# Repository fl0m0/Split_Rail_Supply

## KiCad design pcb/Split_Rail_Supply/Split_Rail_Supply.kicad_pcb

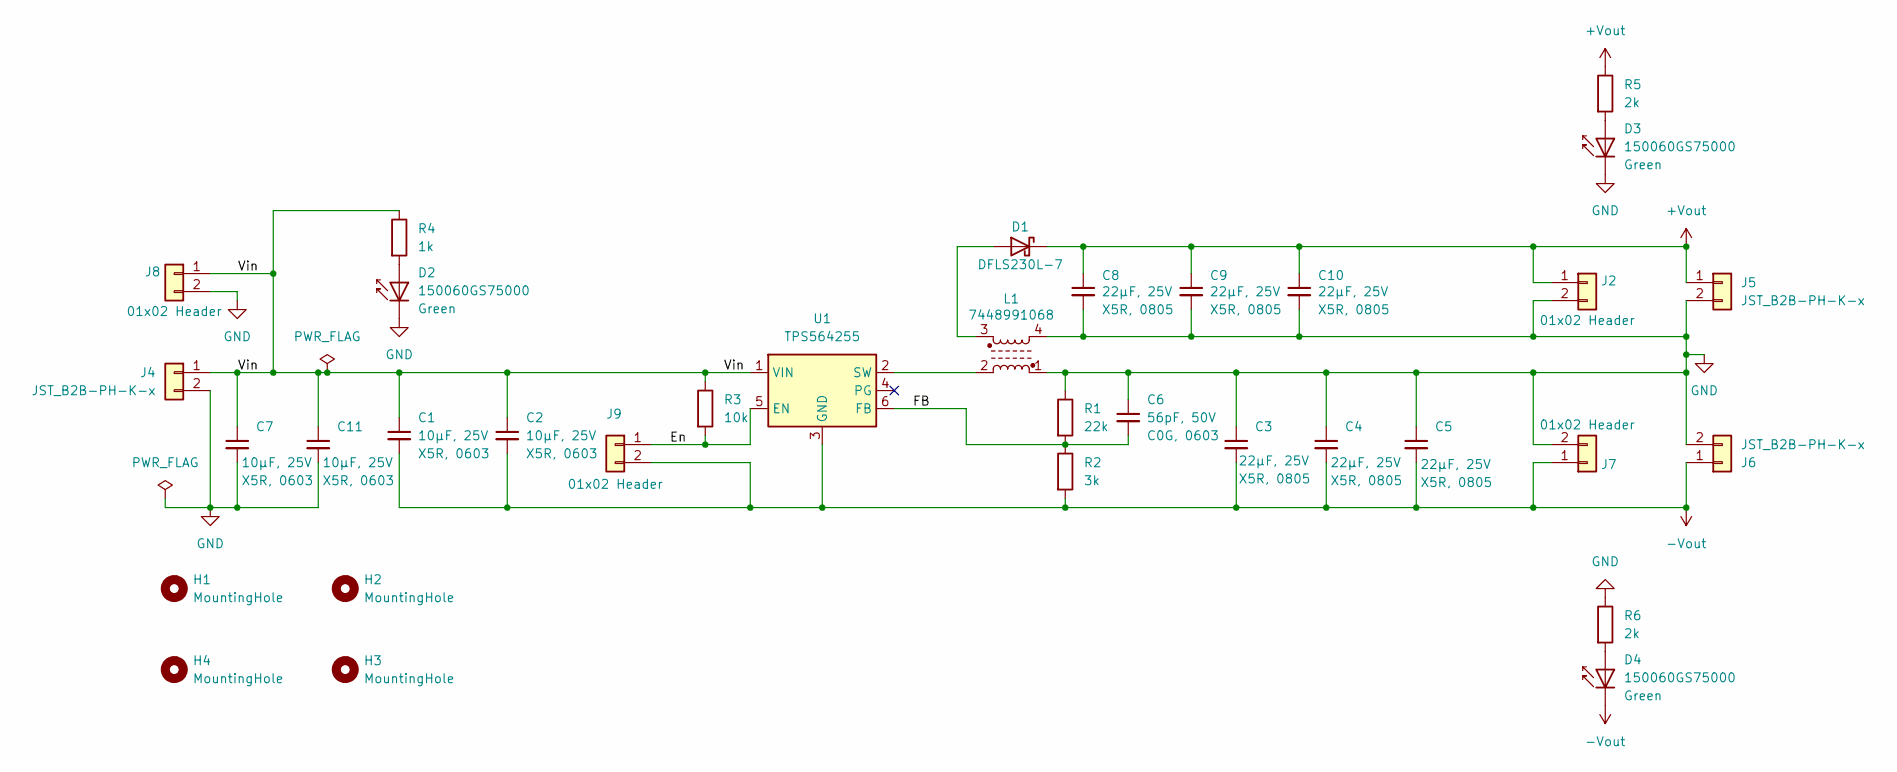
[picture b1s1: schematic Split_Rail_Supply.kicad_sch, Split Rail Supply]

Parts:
C1, C2, C7, C11: 10uF,25V,X5R,0603; C_0603_1608Metric_Pad1.08x0.95mm_HandSolder
C3, C4, C5, C8, C9, C10: 22uF,25V,X5R,0805; C_0805_2012Metric_Pad1.18x1.45mm_HandSolder
C6: 56pF,50V,C0G,0603; C_0603_1608Metric_Pad1.08x0.95mm_HandSolder
D1: DFLS230L-7; D_PowerDI-123; MPN DFLS230L-7
D2, D3, D4: 150060GS75000; LED_0603_1608Metric_Pad1.05x0.95mm_HandSolder
H1, H2, H3, H4: MountingHole; MountingHole_2.7mm_M2.5_DIN965
J2, J7, J8, J9: Header_01x02_Wurth_61300211121; PinHeader_1x02_P2.54mm_Vertical; MPN 61300211121
J4, J5, J6: JST_B2B-PH-K-x; JST_PH_B2B-PH-K_1x02_P2.00mm_Vertical; MPN B2B-PH-K-S(LF)(SN)
L1: 7448991068; L_Wuerth_WE-MCRI-1040_Handsoldering; MPN 7448991068
R1: 22k,0603; R_0603_1608Metric_Pad0.98x0.95mm_HandSolder; Tolerance 1%
R2: 3k,0603; R_0603_1608Metric_Pad0.98x0.95mm_HandSolder; Tolerance 1%
R3: 10k,0603; R_0603_1608Metric_Pad0.98x0.95mm_HandSolder; Tolerance 1%
R4: 1k,0603; R_0603_1608Metric_Pad0.98x0.95mm_HandSolder; Tolerance 1%
R5, R6: 2k,0603; R_0603_1608Metric_Pad0.98x0.95mm_HandSolder; Tolerance 1%
U1: TPS564255; SOT-563; MPN TPS564255DRLR

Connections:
+Vout: C8.1, C9.1, C10.1, D1.1 (K), J2.1, J5.1, R5.1
-Vout: C1.2, C2.2, C3.2, C4.2, C5.2, D4.1 (K), J6.1, J7.1, J9.2, R2.2, U1.3 (GND)
/En: J9.1, R3.2, U1.5 (EN)
/FB: C6.2, R1.2, R2.1, U1.6 (FB)
/Vin: C1.1, C2.1, C7.1, C11.1, J4.1, J8.1, R3.1, R4.1, U1.1 (VIN)
GND: C3.1, C4.1, C5.1, C6.1, C7.2, C8.2, C9.2, C10.2, C11.2, D2.1 (K), D3.1 (K), J2.2, J4.2, J5.2, J6.2, J7.2, J8.2, L1.1, L1.4, R1.1, R6.1
unnamed: D1.2 (A), L1.3
unnamed: D2.2 (A), R4.2
unnamed: D3.2 (A), R5.2
unnamed: D4.2 (A), R6.2
unnamed: L1.2, U1.2 (SW)

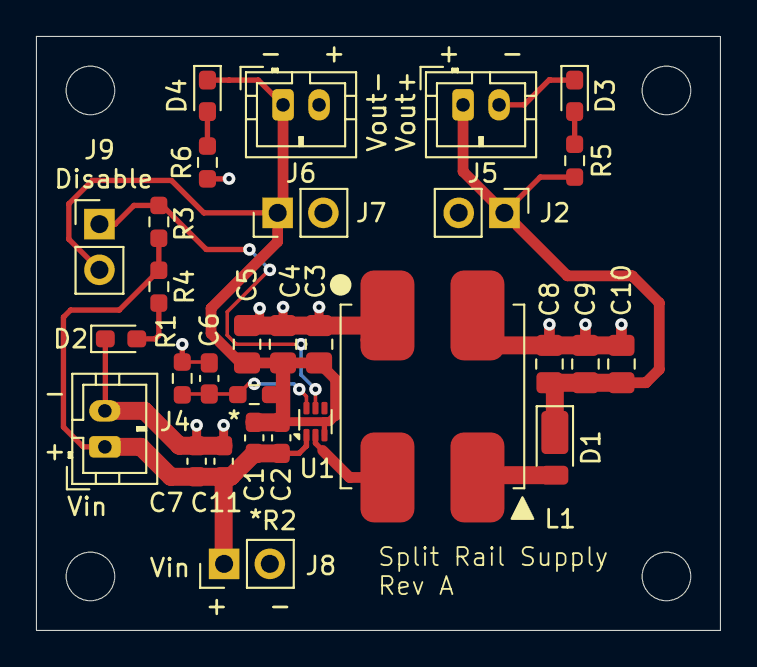
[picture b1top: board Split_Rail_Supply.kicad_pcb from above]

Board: 2 copper layers, 38.0 x 33.0 mm, 34 parts (0 on the bottom side), 11 nets.

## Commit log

2024-10-27 Add docs
2024-10-27 Update SCH, PCB
2024-10-27 Finalize RevA
2024-10-27 Cleanup folders
2024-11-11 Add app notes
2024-11-29 Add app note
